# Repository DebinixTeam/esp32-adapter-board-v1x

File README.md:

# The Amazing ESP32 Adapter Board v1.x

## Use cases 
 
 * This adapter board was used to create a [nautical precision barometer](https://github.com/DebinixTeam/esp32-nautical-barometer-gold) with a unique pressure history function. This [instructable](https://www.instructables.com/Your-Nautical-Barometer-Gold-for-Precise-Weather-F/) documents the project. Find the tested ESP32 modules and pressure sensor in the nautical barometer project [here](https://github.com/DebinixTeam/esp32-nautical-barometer-gold/blob/master/hw-compatibility-list.md).

* The adapter board has numerous I2C header positions for various pressure sensors. However, any I2C breakout board can be used with DuPont wires to match individual signals.

* Almost every ESP32 DIY project requires a TFT SPI display, and this is already built-in. Just plug-and-play. 

* Use the auxiliary connector to test touch panel functionality if the display supports it.

* Use the UART TX port for code debugging.

* Test various ESP32 modules, easy to swap out before deciding which one to put into an actual product.

* The routed GPIO are the ones required for SPI and I2C buses. Thus, it eliminates the breadboard DuPont wire bus rats net!

* Solder `female headers` to the ESP development module, and you have access to all other signals via DuPont wires to a breadboard.

## Specification for The Amazing ESP32 Adapter Board v1.x

This adapter board is fabricated as two layer board with the dimensions 5.4"x6.6" (137.16 x 167.64 mm).

| parameter | imperial | metric |
| -----------|-------|------|
| board material | FR4 | FR4 |
| board thickness | 63 mil | 1.6 mm |
| M3 mounting holes | 1/8" | 3.2 mm |
| header hole diameter | 39.4 mil | 1.0 mm |
| surface finish | HASL (with lead) | HASL (with lead) |
| copper layer thickness | 1.4 mil | 35 um |
| board color | green | green |
| board text | white | white |
| board weight | 2.82 oz | 80 gram |

## Fabrication of the board by yourself

This project is open-source, so that you will find KiCad PCB board design files and gerbers in this repository. Therefore, feel free to modify these files to fit your specific need.

You can directly upload files in the `fabrication/gerbers` folder to PCB prototype services like [OSHPark](https://oshpark.com), [EUROcircuits](https://www.eurocircuits.com/), [JLCPCB](https://jlcpcb.com/), or [PCBWay](https://www.pcbway.com/?adwgc=666&campaignid=172480651&adgroupid=8787904531&feeditemid=&targetid=kwd-96217560494&loc_physical_ms=9077376&matchtype=p&network=g&device=c&devicemodel=&creative=347469560617&keyword=pcbway&placement=&target=&adposition=&gclid=Cj0KCQjw1dGJBhD4ARIsANb6OdmESABFHY6IoLMPbpK8nmhx2egNPqXjOdz1aGUw3X_8KeHwY9J_MfkaAnIwEALw_wcB). Fabrication costs for small quantities vary considerably among suppliers.

## 2.8" 240x320 TFT SPI Display

The board is designed for this particular [2.8" TFT SPI Display](http://www.lcdwiki.com/2.8inch_SPI_Module_ILI9341_SKU:MSP2807). This display can be found on line from various sources, by searching for `SKU:MSP2807`.

## I2C breakout boards

The adapter board uses I2C for various pressure sensors. However, it can still be used for other I2C based breakout boards, either directly if the pin order is identical or using DuPont wires to match individual signals as shown in the [schematic](./kicad/esp32-adapter-schematic-v1x.pdf).

## Female headers

You have the choice to use [female headers](https://www.amazon.com/Glarks-Straight-Connector-Assortment-Prototype/dp/B076GZXW3Z/ref=pd_sbs_3/147-7037756-9410528?pd_rd_w=f0DzS&pf_rd_p=3676f086-9496-4fd7-8490-77cf7f43f846&pf_rd_r=XJ7KEPZZ1EA8WDMJP8NP&pd_rd_r=ec0b5867-c0b8-4d0b-9c31-e0d79fe9c3ec&pd_rd_wg=7Ns6N&pd_rd_i=B076GZXW3Z&psc=1) or permanently `solder` the parts to the board.

## Other sources of the adapter board
You can also purchase the latest designed boards on `Tindie`. 

I appreciate your support.

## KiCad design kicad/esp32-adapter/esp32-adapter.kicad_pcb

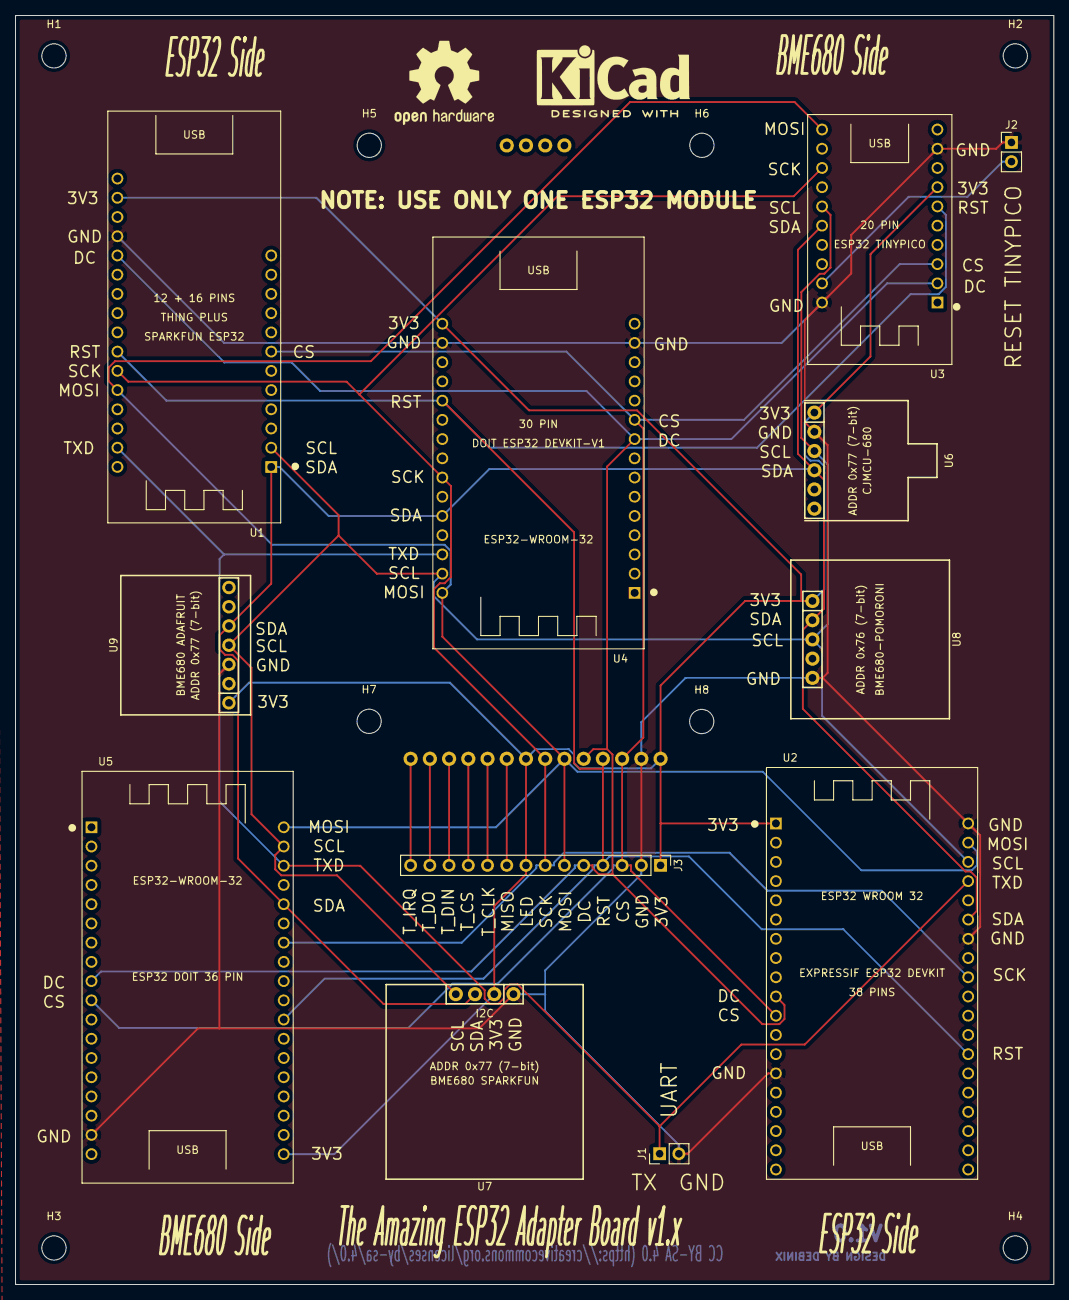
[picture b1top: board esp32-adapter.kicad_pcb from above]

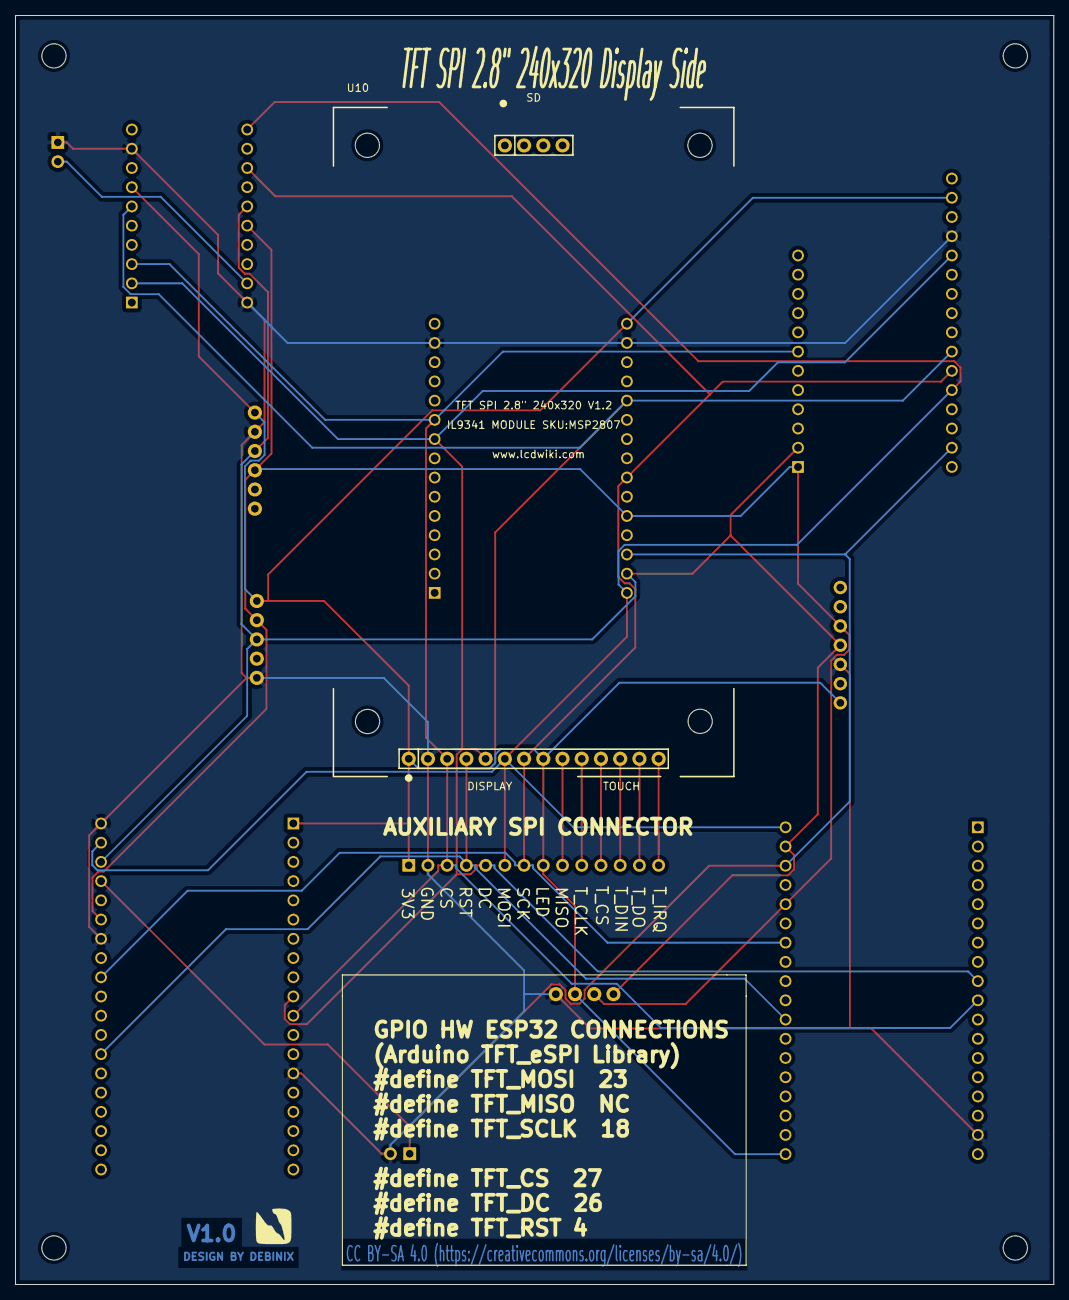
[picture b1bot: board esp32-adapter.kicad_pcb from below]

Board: 2 copper layers, 137.2 x 167.6 mm, 24 parts (2 on the bottom side), 17 nets.

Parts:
G1: LOGO; flash
G2: OSHW-Logo2_14.6x12mm_SilkScreen
G3: KiCad-Logo2_8mm_SilkScreen
H1, H2, H3, H4, H5, H6, H7, H8: MountingHole_3.2mm_M3
J1: DEBUG; PinHeader_1x02_P2.54mm_Vertical
J2: SHRT TO RESET; PinHeader_1x02_P2.54mm_Vertical
J3: TFT_SPI_CONN; PinHeader_1x14_P2.54mm_Vertical
U1: ESP32-THINGS-PLUS; SPARKFUN_ESP32-THING-PLUS
U2: ESP32-DEVKITC-32D; MODULE_ESP32-DEVKITC-32D
U3: ESP32-TINYPICO; ESP32_TINY_PICO
U4: ESP32-DOIT-30PIN
U5: ESP32-DOIT-36PIN
U6: CJMCU-680; BME680-CJMCU-680
U7: Sparkfun-BME680; BME680-SPARKFUN
U8: Pimoroni-BME680; BME680-PIMORONI
U9: Adafruit-BME680; BME680-ADAFRUIT
U10: IL9341-240x320-TFT-LCD; IL9341-TFTSPI-240x320V1_2

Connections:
+3V3: J3.1, J3.8, U1.27, U2.1, U3.7, U4.30, U5.36, U6.1, U7.2, U8.1, U9.1, U10.1, U10.8
CS: J3.3, U1.7, U2.11, U3.3, U4.10, U5.10, U10.3
DC: J3.5, U1.24, U2.10, U3.2, U4.9, U5.9, U10.5
GND: J1.2, J2.1, J3.2, U1.25, U2.14, U2.20, U2.26, U3.9, U3.11, U4.14, U4.29, U5.17, U6.2, U7.1, U8.5, U9.3, U10.2
MISO: J3.9, U10.9
MOSI: J3.6, U1.17, U2.21, U3.20, U4.16, U5.19, U10.6
unnamed: J2.2, U3.12
RST: J3.4, U1.19, U2.32, U3.6, U4.26, U5.29, U10.4
SCK: J3.7, U1.18, U2.28, U3.18, U4.22, U5.25, U10.7
SCL: U1.2, U2.22, U3.16, U4.17, U5.20, U6.3, U7.4, U8.3, U9.4
SDA: U1.1, U2.25, U3.15, U4.20, U5.23, U6.4, U7.3, U8.2, U9.5
TXD: J1.1, U1.14, U2.23, U4.18, U5.21
T_CLK: J3.10, U10.10
T_CS: J3.11, U10.11
T_DIN: J3.12, U10.12
T_DO: J3.13, U10.13
T_IRQ: J3.14, U10.14

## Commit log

2021-09-10 upate tindie link
2021-09-12 add use cases
2021-09-13 add link to compatibility list
2021-09-16 update link

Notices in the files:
kicad/esp32-adapter/esp32-adapter.kicad_pcb:
Licence: CC BY-SA 4.0
CC BY-SA 4.0 (https://creativecommons.org/licenses/by-sa/4.0/)
